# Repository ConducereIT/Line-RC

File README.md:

# Line RC (inca n-am gasit nume)
## Structura 

Line RC este un robot line follower homebrew facut pentru Robochallange. Foloseste un ESP32 ca si microcontroller pentru avantajul de Update OTA, compatibilitatea cu majoritatea librariilor deja existente, simplitatea implementarii si pentru cele doua nuclee.
Design-ul urmareste o structura "prevazatoare", tintind spre redundanta, fara a compromite capacitatea de expansiune/depanare rapida/procesare.

## Bara de senzori

Bara de senzori este dezvoltata in jurul placilor XLINE de la JSumo, datorita rezilientei lor si a simplitatii design-ului. Bara este formata din 16 senzori IR conectati la un D/MUX analogic ce poate conecta fiecare dintre acestia direct la un pin ADC. Pe langa asta, bara mai dispune si de un connector FFC dar si de pini header de 2,54 mm.
Astfel, devenind compatibila cu barile XLINE si "detasata" de robot, design-ul putand fi folosit si cu alte placi de dezvoltare.

### Status:

- [x] PCB in mare parte
- [x] BOM
- [x] Schema
- [x] Foldere / subfoldere
- [ ] Gauri pentru tijele de suport
- [ ] Test points
- [ ] LED pentru status

## PCB Main

Este construit pentru compatibilitate cu acumulatori LiPO 2S1P, folosind mufe XT60. Placa are la dispozitie un port USB tip C pentru programare/debuggind, folosind un traductor de la USB la UART. Alimentarea circuitelor se poate face in doua moduri, fie folosind circuitul de buck intern, fie cel de pe ESC, selectia fiind facuta prin lipirea a unor pad-uri.
Avantajul acestei abordari este separarea datoriilor de OVP/OCP intre PCB si ESC, pentru a asigura ca si in cel mai nefavorabil caz, circuitul main inca poate fi folosit. Placa dispune si de un regulator liniar de 3.3V pentru a alimenta ESP-ul cat si o parte din electronica pentru achizitia de date (Bara de senzori). Desi ESP-ul are integrat un LDO, este mai usor/ieftin de schimbat un LDO decat un ESP.
Yappa yappa drivere yappa yappa motoare N20 yappa yappa turbina sau fara turbina yappa yappa

- [x] Schema
- [x] BOM
- [ ] PCB
- [ ] Test points
- [ ] Mufe extra pentru GPIO
- [ ] Gauri pentru tijele de suport
- [ ] Gaura pentru turbina
- [ ] Placement LiPo / ESC
- [ ] Roti
- [ ] LED Status

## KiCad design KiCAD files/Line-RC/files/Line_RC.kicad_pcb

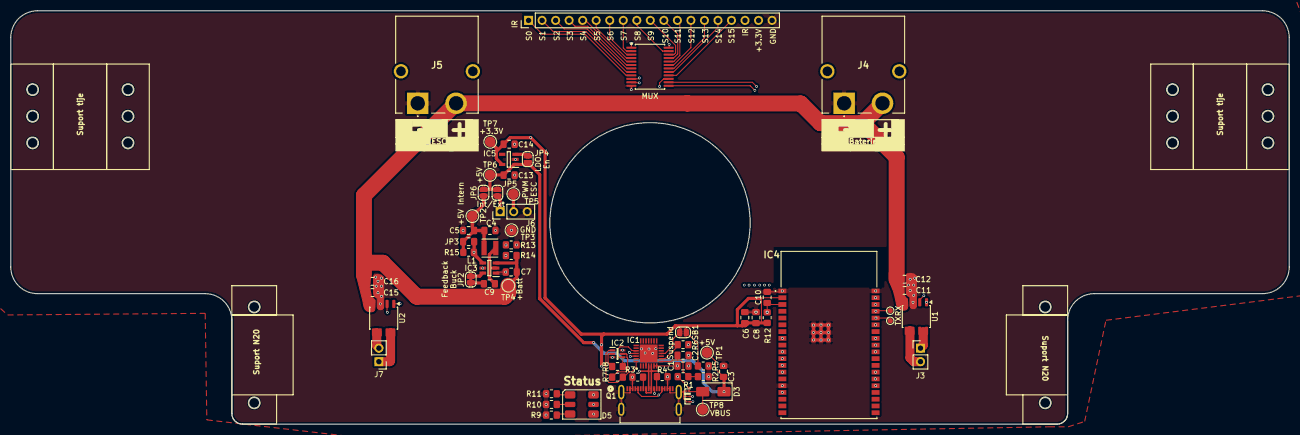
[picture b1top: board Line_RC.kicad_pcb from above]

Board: 4 copper layers, 239.9 x 77.5 mm, 68 parts (0 on the bottom side), 50 nets.

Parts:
C1: 10uF/25V; C_0805_2012Metric_Pad1.18x1.45mm_HandSolder
C2: 1uF/ 16V (10%); C_0805_2012Metric_Pad1.18x1.45mm_HandSolder
C3: 10uF/25V (20%); C_0805_2012Metric_Pad1.18x1.45mm_HandSolder
C4: 22uF; C_0805_2012Metric_Pad1.18x1.45mm_HandSolder
C5, C7: 10uF; C_0805_2012Metric_Pad1.18x1.45mm_HandSolder
C6: 22uF/10V; C_0805_2012Metric_Pad1.18x1.45mm_HandSolder
C8, C10, C12, C16: 100nF/50V; C_0805_2012Metric_Pad1.18x1.45mm_HandSolder
C9: 100nF; C_0805_2012Metric_Pad1.18x1.45mm_HandSolder
C11, C15: 47uF/16V; C_0805_2012Metric_Pad1.18x1.45mm_HandSolder
C13, C14: 1uF/ 16V; C_0805_2012Metric_Pad1.18x1.45mm_HandSolder
D1, D2, D4: STN061050BL15; Infineon_SG-WLL-2-3_0.58x0.28_P0.36mm
D3: SS14; D_SMA
D5: Inolux_IN-P55TATRGB; LED_Inolux_IN-P55TATRGB_PLCC6_5.0x5.5mm_P1.8mm
IC1: CP2102N-A02-GQFN28R; QFN50P500X500X80-29N-D
IC2: BC847BDW1T1G; SOT65P210X110-6N
IC3: TPS563240DDCR; SOT95P280X110-6N
IC4: ESP32-WROVER-E-N4R8; ESP32WROVEREN4R8
IC5: TLV75533PDBVR; SOT95P280X145-5N
IR: PinHeader_1x19_P2.54mm_Vertical
J3, J7: Motor OUT; PinHeader_1x02_P2.54mm_Vertical
J4, J5: XT60PW-M; XT60PWM
J6: Conn_01x03_ESC; PinHeader_1x03_P2.54mm_Vertical
JP2: 0R; SolderJumper-2_P1.3mm_Bridged_RoundedPad1.0x1.5mm
JP3: C4; C_0805_2012Metric_Pad1.18x1.45mm_HandSolder
JP4: Solder Bridge; SolderJumper-2_P1.3mm_Open_RoundedPad1.0x1.5mm
JP5: Buck Ext; SolderJumper-2_P1.3mm_Open_RoundedPad1.0x1.5mm
JP6: Buck Int; SolderJumper-2_P1.3mm_Open_RoundedPad1.0x1.5mm
L1: 1.5uH; L_Neosid_SMS-ME3015
MUX: SSOP-24_5.3x8.2mm_P0.65mm
Q1: CX90M-16P_HIR
R1: 22.1k (1%); R_0805_2012Metric_Pad1.20x1.40mm_HandSolder
R2: 47.5k (1%); R_0805_2012Metric_Pad1.20x1.40mm_HandSolder
R3, R4: 5.1K 1%; R_0805_2012Metric_Pad1.20x1.40mm_HandSolder
R5, R12: 10k (1%); R_0805_2012Metric_Pad1.20x1.40mm_HandSolder
R6: 1k (1%); R_0805_2012Metric_Pad1.20x1.40mm_HandSolder
R7, R8, R13, R14: 10k; R_0805_2012Metric_Pad1.20x1.40mm_HandSolder
R9, R10, R11: 1k; R_0805_2012Metric_Pad1.20x1.40mm_HandSolder
R15: 73.2k; R_0805_2012Metric_Pad1.20x1.40mm_HandSolder
SB1: Solder Bridge; SolderJumper-2_P1.3mm_Open_RoundedPad1.0x1.5mm
TP1: 5V USB; TestPoint_Pad_D2.0mm
TP2: 5v_intern; TestPoint_Pad_D2.0mm
TP3: GND; TestPoint_Pad_D2.0mm
TP4: Batt; TestPoint_Pad_D2.0mm
TP5: PWM; TestPoint_Pad_D2.0mm
TP6, TP7, TP8: 5V rail; TestPoint_Pad_D2.0mm
TP9, TP10: RX; TestPoint_Pad_D2.0mm
U1, U2: SSOP-8_3.9x5.05mm_P1.27mm

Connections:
+3.3V: C1.1, C6.1, C8.1, C14.1, IC1.6 (VDD), IC1.7 (VREGIN), IC4.2 (3V3), IC5.5 (OUT), IR.17, IR.18, MUX.24, R6.2, R12.2, TP7.1 (1_1)
+5V: C3.1, C13.1, D3.1 (K), IC5.1 (IN), JP4.1 (A), JP5.2 (B), JP6.1 (A), TP1.1 (1_1), TP6.1 (1_1)
+5V_Int: C4.1, C5.1, JP3.2 (B), JP6.2 (B), L1.1, R15.1, TP2.1 (1_1)
+BATT: C7.1, C11.1, C12.1, C15.1, C16.1, IC3.3 (VIN), J4.2 (Vcc), J5.2 (Vcc), R14.2, TP4.1 (1_1), U1.4 (VCC), U2.4 (VCC)
A1: IC4.26 (IO4), U1.2 (FI)
A2: IC4.29 (IO5), U1.1 (BI)
B: D5.6 (AB), IC4.24 (IO2)
B1: IC4.30 (IO18), U2.2 (FI)
B2: IC4.31 (IO19), U2.1 (BI)
DTR: IC1.28 (DTR), IC2.1 (E2), R7.2
EN: C10.1, IC2.3 (C1), IC4.3 (EN), R12.1
G: D5.4 (AG), IC4.37 (IO23)
GND: C1.2, C2.2, C3.2, C4.2, C5.2, C6.2, C7.2, C8.2, C10.2, C11.2, C12.2, C13.2, C14.2, C15.2, C16.2, D1.1 (A1), D2.1 (A1), D4.1 (A1), IC1.3 (GND_1), IC1.29 (GND_2), IC3.1 (GND), IC4.1 (GND_1), IC4.15 (GND_2), IC4.38 (GND_3), IC4.39 (GND_4), IC4.40 (GND_5), IC4.41 (GND_6), IC4.42 (GND_7), IC4.43 (GND_8), IC4.44 (GND_9), IC4.45 (GND_10), IC4.46 (GND_11), IC4.47 (GND_12), IC5.2 (GND), IR.19, J4.1 (GND), J5.1 (GND), J6.3, MUX.12, Q1.A1, Q1.A12, Q1.B1, Q1.B12, R2.2, R3.2, R4.2, R5.2, R9.2, R10.2, R11.2, R13.1, TP3.1 (1_1), U1.3 (GND), U2.3 (GND)
GPIO0: IC2.6 (C2), IC4.25 (IO0)
unnamed: D5.1 (KB), R11.1
unnamed: D5.3 (KG), R9.1
unnamed: D5.2 (KR), R10.1
unnamed: IC1.9 (RSTB), R6.1
unnamed: IC1.11 (SUSPENDB), SB1.1 (A)
unnamed: C2.1, IC1.8 (VBUS), R1.2, R2.1
unnamed: IC2.5 (B1), R7.1
unnamed: IC2.2 (B2), R8.2
unnamed: IC3.5 (EN), R14.1
unnamed: C9.1, IC3.2 (SW), L1.2
unnamed: IC3.6 (VBST), JP2.2 (B)
unnamed: IC3.4 (VFB), JP3.1 (A), R13.2, R15.2
unnamed: IC5.3 (EN), JP4.2 (B)
unnamed: J3.1, U1.7 (BO), U1.8 (BO)
unnamed: J3.2, U1.5 (FO), U1.6 (FO)
unnamed: J6.1, JP5.1 (A)
unnamed: J7.1, U2.7 (BO), U2.8 (BO)
unnamed: J7.2, U2.5 (FO), U2.6 (FO)
unnamed: R5.1, SB1.2 (B)
unnamed: C9.2, JP2.1 (A)
unnamed: Q1.B5, R4.1
unnamed: Q1.B8, R3.1
PWM: IC4.33 (IO21), J6.2, TP5.1 (1_1)
R: D5.5 (AR), IC4.36 (IO22)
RTS: IC1.24 (RTS), IC2.4 (E1), R8.1
RXD0: IC1.26 (TXD), IC4.35 (TXD0), TP9.1 (1_1)
S0: IC4.10 (IO25), MUX.10
S1: IC4.11 (IO26), MUX.11
S2: IC4.12 (IO27), MUX.14
S3: IC4.13 (IO14), MUX.13
TXD0: IC1.25 (RXD), IC4.34 (RXD0), TP10.1 (1_1)
USB_D+: D4.2 (A2), IC1.4 (D+), Q1.A7, Q1.B7
USB_D-: D2.2 (A2), IC1.5 (D-), Q1.A6, Q1.B6
VBUS: D1.2 (A2), D3.2 (A), Q1.A4, Q1.A9, Q1.B4, Q1.B9, R1.1, TP8.1 (1_1)
Z: IC4.8 (IO32), MUX.1
~E: IC4.16 (IO13), MUX.15

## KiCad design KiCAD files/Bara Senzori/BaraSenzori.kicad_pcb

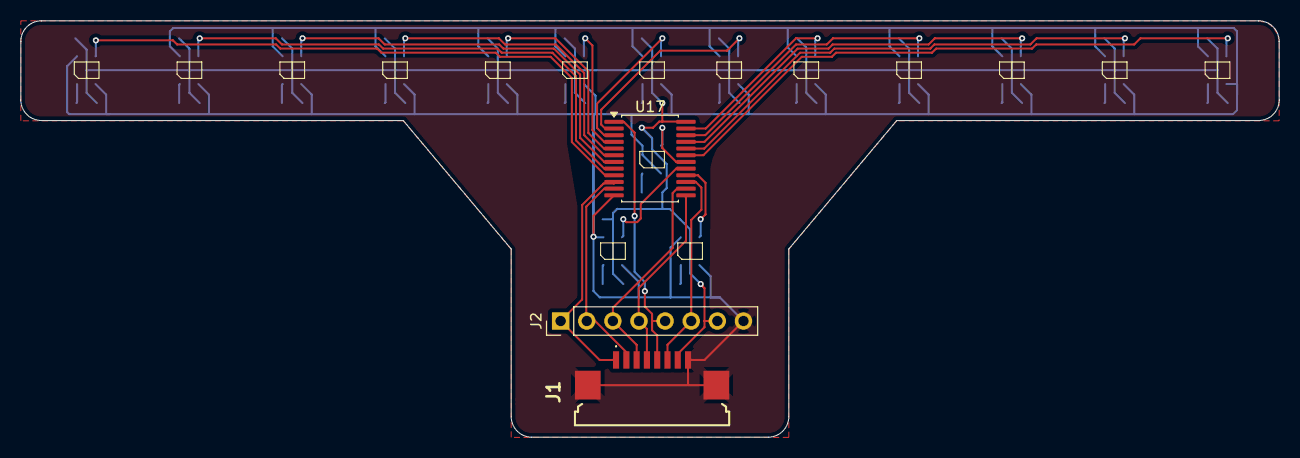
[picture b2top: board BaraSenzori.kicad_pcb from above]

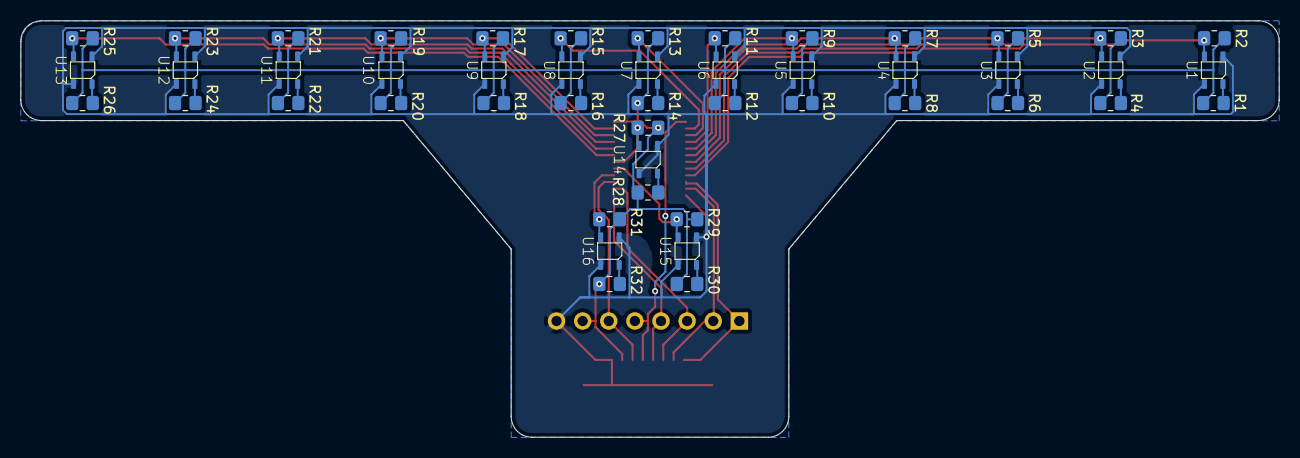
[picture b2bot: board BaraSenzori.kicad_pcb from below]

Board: 2 copper layers, 122.4 x 40.5 mm, 51 parts (48 on the bottom side), 40 nets.

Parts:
J1: FFC3B07-08-T; FFC3B0708T
J2: PinHeader_1x08_P2.54mm_Vertical
R1, R4, R6, R8, R10, R12, R14, R16, R18, R20, R22, R24, R26, R28, R30, R32: 100; R_0805_2012Metric_Pad1.20x1.40mm_HandSolder
R2, R3, R5, R7, R9, R11, R13, R15, R17, R19, R21, R23, R25, R27, R29, R31: 6.8k; R_0805_2012Metric_Pad1.20x1.40mm_HandSolder
U1, U2, U3, U4, U5, U6, U7, U8, U9, U10, U11, U12, U13, U14, U15, U16: ITR8307
U17: CD74HC4067SM; SSOP-24_5.3x8.2mm_P0.65mm

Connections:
+3.3V: J1.7, J2.7, R1.1, R2.1, R3.1, R4.1, R5.1, R6.1, R7.1, R8.1, R9.1, R10.1, R11.1, R12.1, R13.1, R14.1, R15.1, R16.1, R17.1, R18.1, R19.1, R20.1, R21.1, R22.1, R23.1, R24.1, R25.1, R26.1, R27.1, R28.1, R29.1, R30.1, R31.1, R32.1, U17.24 (VCC)
GND: J1.8, J1.9 (MP_1), J1.10 (MP_2), J2.8, U1.1, U1.4, U2.1, U2.4, U3.1, U3.4, U4.1, U4.4, U5.1, U5.4, U6.1, U6.4, U7.1, U7.4, U8.1, U8.4, U9.1, U9.4, U10.1, U10.4, U11.1, U11.4, U12.1, U12.4, U13.1, U13.4, U14.1, U14.4, U15.1, U15.4, U16.1, U16.4, U17.12 (GND)
unnamed: R1.2, U1.2
unnamed: R4.2, U2.2
unnamed: R6.2, U3.2
unnamed: R8.2, U4.2
unnamed: R10.2, U5.2
unnamed: R12.2, U6.2
unnamed: R14.2, U7.2
unnamed: R16.2, U8.2
unnamed: R18.2, U9.2
unnamed: R20.2, U10.2
unnamed: R22.2, U11.2
unnamed: R24.2, U12.2
unnamed: R26.2, U13.2
unnamed: R28.2, U14.2
unnamed: R30.2, U15.2
unnamed: R32.2, U16.2
unnamed: J1.5, J2.5, U17.1 (COM)
unnamed: J1.1, J2.1, U17.10 (S0)
unnamed: J1.2, J2.2, U17.11 (S1)
unnamed: J1.3, J2.3, U17.14 (S2)
unnamed: J1.4, J2.4, U17.13 (S3)
unnamed: J1.6, J2.6, U17.15 (~E)
S0: R2.2, U1.3, U17.9 (I0)
S1: R3.2, U2.3, U17.8 (I1)
S2: R5.2, U3.3, U17.7 (I2)
S3: R7.2, U4.3, U17.6 (I3)
S4: R9.2, U5.3, U17.5 (I4)
S5: R11.2, U6.3, U17.4 (I5)
S6: R13.2, U7.3, U17.3 (I6)
S7: R15.2, U8.3, U17.2 (I7)
S8: R17.2, U9.3, U17.23 (I8)
S9: R19.2, U10.3, U17.22 (I9)
S10: R21.2, U11.3, U17.21 (I10)
S11: R23.2, U12.3, U17.20 (I11)
S12: R25.2, U13.3, U17.19 (I12)
S13: R27.2, U14.3, U17.18 (I13)
S14: R29.2, U15.3, U17.17 (I14)
S15: R31.2, U16.3, U17.16 (I15)

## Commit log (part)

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2026-06-29 Revise README for project clarity
    Updated project description to clarify multiple variants.
2026-06-29 Added the KiCAD files, schematic, structured files
2026-06-29 bleh bleh
